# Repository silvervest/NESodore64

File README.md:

# NESodore64

NESodore64 is an AVR microcontroller board that interfaces with an original NES controller pad, and outputs signals that emulate a joystick for Commodore 64's. It might be used on other computers of the era, but I haven't tested it on any and guarantee nothing!

It's creation was documented in [this YouTube video](https://youtu.be/1u0i-EAIm1I)

## Pin details

Here's some tables describing the pins and their connections found or used as part of this project.

### NES pad

The NES pad seems to have identical wire colours, as they are specifically written on the back which colour goes where, but not which wire does what, so here's that chart for ya.

| Colour | Pin | Purpose |
|--------|-----|---------|
| Brown  | 1   | Ground  |
| Red    | 2   | Clock   |
| Orange | 3   | Latch   |
| Yellow | 4   | Data    |
| White  | 7   | +5V     |

### C64 joystick

A LOT more detail about the port at https://www.c64-wiki.com/wiki/Control_Port.

In the joystick I used, however, these were the wire colours. Your joystick will PROBABLY have different colours, so unless you have the exact one used in my video, don't use this as a guide. Even then, just buzz the wires out yourself to be sure!

| Colour | Pin | Purpose   | 
|--------|-----|-----------|
| White  | 1   | Joy UP    |
| Blue   | 2   | Joy DOWN  |
| Green  | 3   | Joy LEFT  |
| Brown  | 4   | Joy RIGHT |
| Yellow | 5   | Paddle Y  |
| Orange | 6   | But FIRE  |
| Red    | 7   | +5V       |
| Black  | 8   | Ground    |
| Grey   | 9   | Paddle X  |

## Contributing
Pull requests are welcome. For major changes, please open an issue first to discuss what you would like to change.

Please make sure to update tests as appropriate.

## License
[MIT](https://choosealicense.com/licenses/mit/)

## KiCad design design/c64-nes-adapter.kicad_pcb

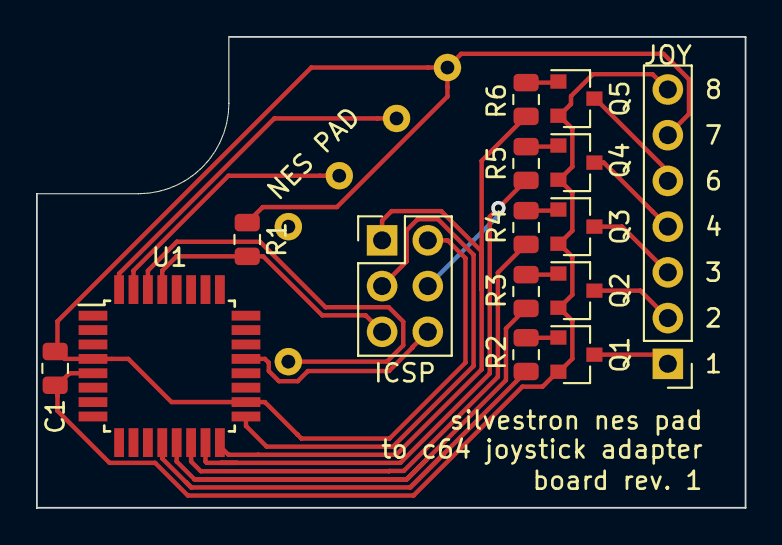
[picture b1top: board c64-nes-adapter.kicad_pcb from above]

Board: 2 copper layers, 39.4 x 26.2 mm, 16 parts (0 on the bottom side), 22 nets.

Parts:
C1: 0.1uF; C_0805_2012Metric
ICSP: ICSP; PinHeader_2x03_P2.54mm_Vertical
JOY: C64 joystick; PinHeader_1x07_P2.54mm_Vertical
NES PAD: NES board; NES_Dpad_Conn
Q1, Q2, Q3, Q4, Q5: BC847; SOT-23
R1: 10k; R_0805_2012Metric
R2, R3, R4, R5, R6: 4k7; R_0805_2012Metric
U1: ATmega328PB-AU; TQFP-32_7x7mm_P0.8mm

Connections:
+5V: C1.1, ICSP.2, JOY.7, NES PAD.1, R1.1, U1.4, U1.18
GND: C1.2, ICSP.6, JOY.8, NES PAD.5, Q1.2, Q2.2, Q3.2, Q4.2, Q5.2, U1.5, U1.21
unnamed: NES PAD.2, U1.31
unnamed: NES PAD.3, U1.32
unnamed: NES PAD.4, U1.30
unnamed: JOY.1, Q1.3
unnamed: JOY.2, Q2.3
unnamed: JOY.3, Q3.3
unnamed: JOY.4, Q4.3
unnamed: JOY.6, Q5.3
unnamed: ICSP.1, R6.2, U1.16
unnamed: ICSP.3, U1.17
unnamed: ICSP.4, R5.2, U1.15
unnamed: ICSP.5, R1.2, U1.29
unnamed: Q1.1, R2.1
unnamed: Q2.1, R3.1
unnamed: Q3.1, R4.1
unnamed: Q4.1, R5.1
unnamed: Q5.1, R6.1
unnamed: R2.2, U1.12
unnamed: R3.2, U1.13
unnamed: R4.2, U1.14
